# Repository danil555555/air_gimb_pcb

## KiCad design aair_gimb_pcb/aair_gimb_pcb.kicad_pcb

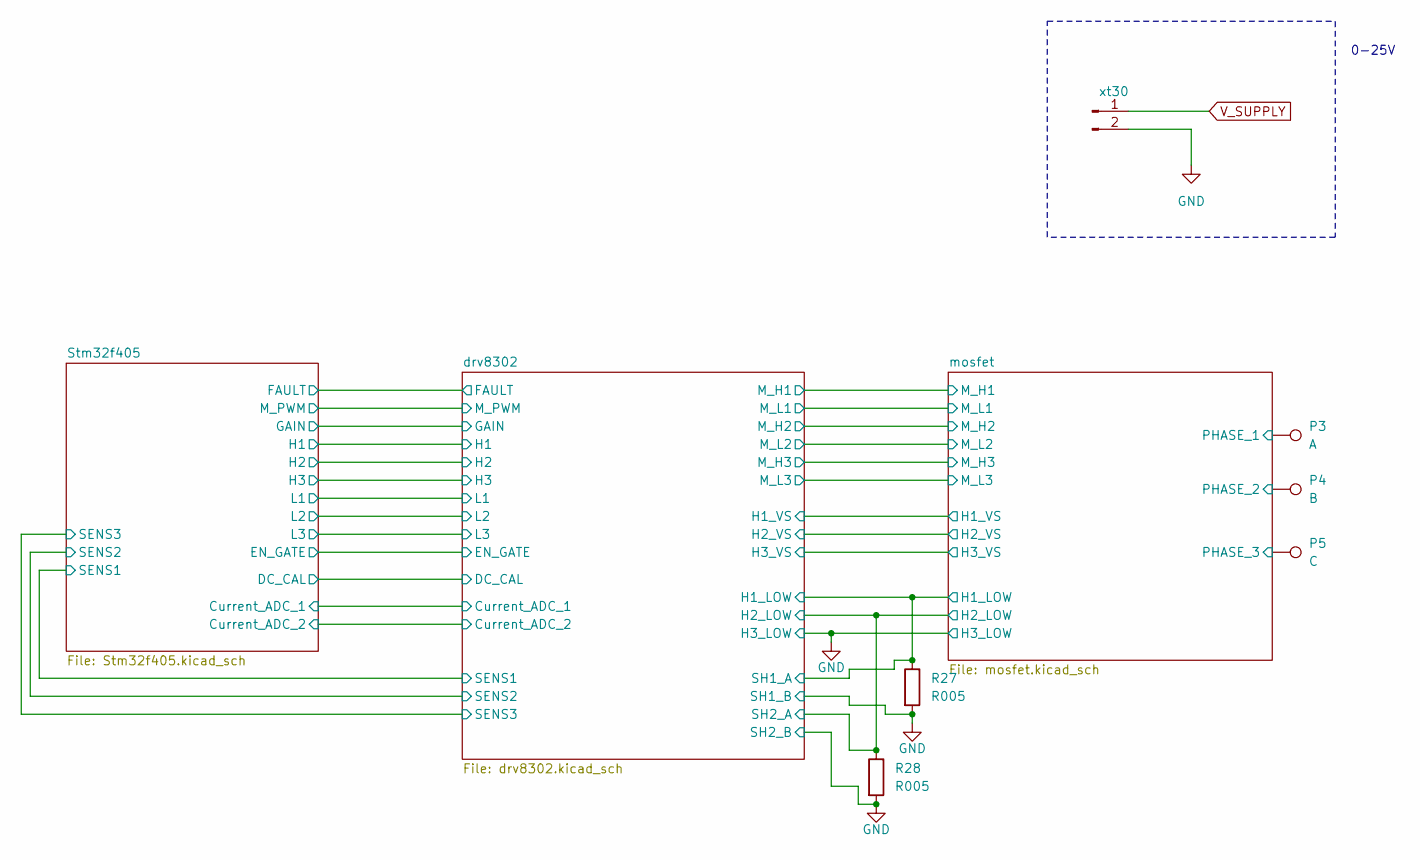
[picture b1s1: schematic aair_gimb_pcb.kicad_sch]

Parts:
P3: A; 1PAD_4x5mm
P4: B; 1PAD_4x5mm
P5: C; 1PAD_4x5mm
R27, R28: R005; R_2512_6332Metric
xt30: XT30; AMASS_XT30PW-M_1x02_P2.50mm_Horizontal

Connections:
/drv8302/H1_LOW: R27.1; also elsewhere on the board
/drv8302/H2_LOW: R28.1; also elsewhere on the board
GND: R27.2, R28.2, xt30.2; also elsewhere on the board
V_SUPPLY: xt30.1; also elsewhere on the board

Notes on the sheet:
0-25V

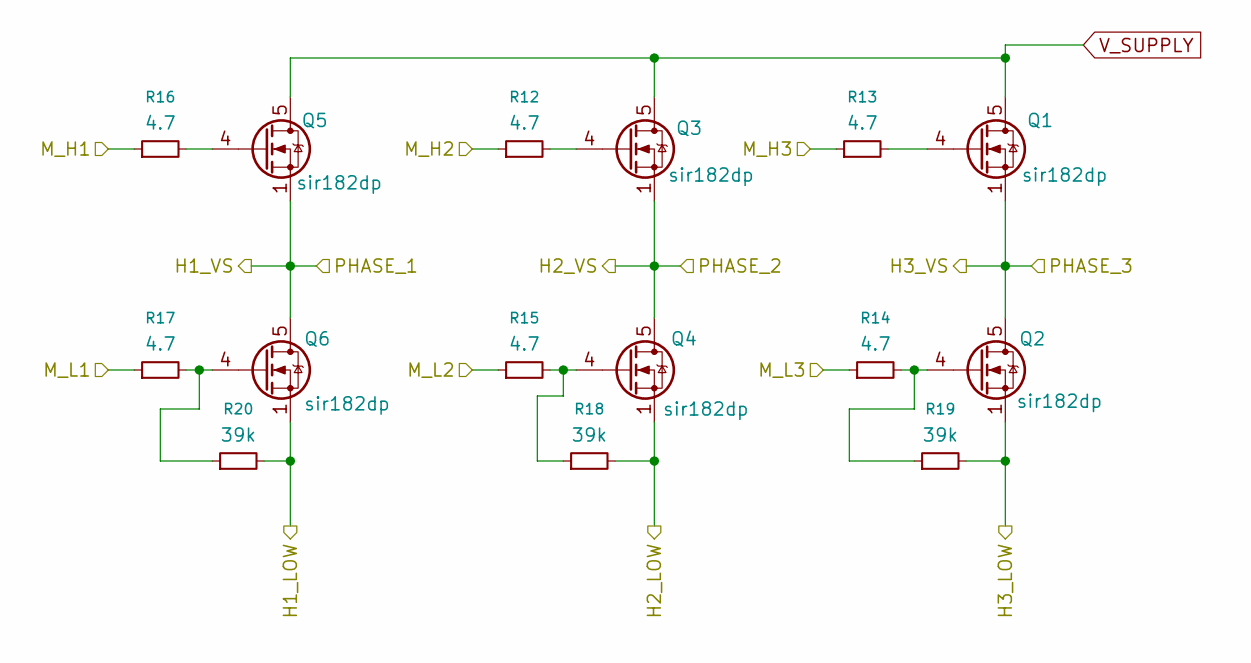
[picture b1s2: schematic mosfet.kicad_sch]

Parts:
Q1, Q2, Q3, Q4, Q5, Q6: sir182dp; PowerPAK_SO-8_Single
R12, R13, R14, R15, R16, R17: 4.7; R_0603_1608Metric
R18, R19, R20: 39k; R_0603_1608Metric

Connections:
/drv8302/H1_LOW: Q6.1 (S), Q6.2 (S), Q6.3 (S), R20.2; also elsewhere on the board
/drv8302/H1_VS: Q5.1 (S), Q5.2 (S), Q5.3 (S), Q6.5 (D); also elsewhere on the board
/drv8302/H2_LOW: Q4.1 (S), Q4.2 (S), Q4.3 (S), R18.2; also elsewhere on the board
/drv8302/H2_VS: Q3.1 (S), Q3.2 (S), Q3.3 (S), Q4.5 (D); also elsewhere on the board
/drv8302/H3_VS: Q1.1 (S), Q1.2 (S), Q1.3 (S), Q2.5 (D); also elsewhere on the board
/drv8302/M_H1: R16.1; also elsewhere on the board
/drv8302/M_H2: R12.1; also elsewhere on the board
/drv8302/M_H3: R13.1; also elsewhere on the board
/drv8302/M_L1: R17.1; also elsewhere on the board
/drv8302/M_L2: R15.1; also elsewhere on the board
/drv8302/M_L3: R14.1; also elsewhere on the board
GND: Q2.1 (S), Q2.2 (S), Q2.3 (S), R19.2; also elsewhere on the board
unnamed: Q1.4 (G), R13.2
unnamed: Q2.4 (G), R14.2, R19.1
unnamed: Q3.4 (G), R12.2
unnamed: Q4.4 (G), R15.2, R18.1
unnamed: Q5.4 (G), R16.2
unnamed: Q6.4 (G), R17.2, R20.1
V_SUPPLY: Q1.5 (D), Q3.5 (D), Q5.5 (D); also elsewhere on the board

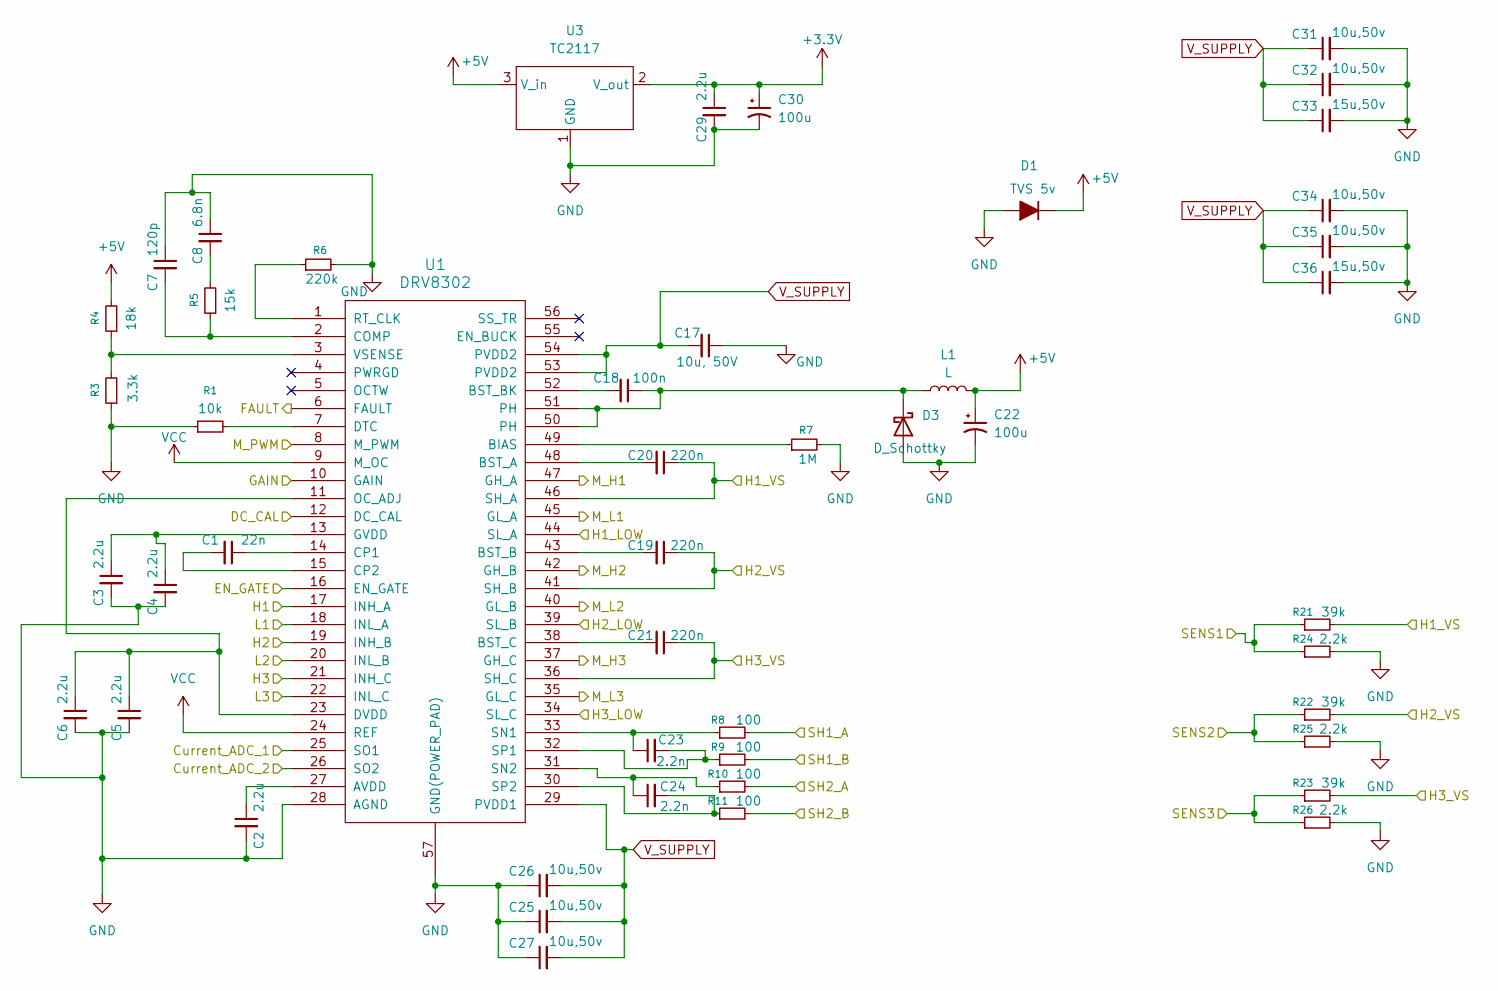
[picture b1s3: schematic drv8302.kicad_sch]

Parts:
C1: 22n; SMD-0603_r
C2, C3, C4, C6, C29: 2.2u; SMD-0603_r
C5: 2.2u; SMD-0603_c
C7: 120p; SMD-0603_r
C8: 6.8n; SMD-0603_r
C17: 10u, 50V; SMD-1206
C18: 100n; SMD-0603_r
C19, C20, C21: 220n; SMD-0603_r
C22, C30: 100u; CP_EIA-3528-21_Kemet-B
C23, C24: 2.2n; SMD-0603_r
C25, C26, C27, C31, C32, C34, C35: 10u,50v; C_1206_3216Metric
C33, C36: 15u,50v; C_1206_3216Metric
D1: TVS 5v; D_SMA
D3: D_Schottky; D_SMA
L1: L; L_7.3x7.3_H4.5
R1: 10k; SMD-0603_r
R3: 3.3k; SMD-0603_r
R4: 18k; SMD-0603_r
R5: 15k; SMD-0603_r
R6: 220k; SMD-0603_r
R7: 1M; SMD-0603_r
R8, R9, R10, R11: 100; SMD-0603_r
R21, R22, R23: 39k; SMD-0603_r
R24, R25, R26: 2.2k; SMD-0603_r
U1: DRV8302; HTSSOP-56-1EP_6.1x14mm_P0.5mm_EP3.61x6.35mm
U3: TC2117; SOT-223

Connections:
+3.3V: C29.1, C30.1, U3.2 (V_out); also elsewhere on the board
+5V: C22.1, D1.1 (K), L1.2, R4.2, U3.3 (V_in); also elsewhere on the board
/Stm32f405/Current_ADC_1: U1.25 (SO1); also elsewhere on the board
/Stm32f405/Current_ADC_2: U1.26 (SO2); also elsewhere on the board
/Stm32f405/DC_CAL: U1.12 (DC_CAL); also elsewhere on the board
/Stm32f405/EN_GATE: U1.16 (EN_GATE); also elsewhere on the board
/Stm32f405/FAULT: U1.6 (FAULT); also elsewhere on the board
/Stm32f405/GAIN: U1.10 (GAIN); also elsewhere on the board
/Stm32f405/H1: U1.17 (INH_A); also elsewhere on the board
/Stm32f405/H2: U1.19 (INH_B); also elsewhere on the board
/Stm32f405/H3: U1.21 (INH_C); also elsewhere on the board
/Stm32f405/L1: U1.18 (INL_A); also elsewhere on the board
/Stm32f405/L2: U1.20 (INL_B); also elsewhere on the board
/Stm32f405/L3: U1.22 (INL_C); also elsewhere on the board
/Stm32f405/M_PWM: U1.8 (M_PWM); also elsewhere on the board
/Stm32f405/SENS1: R21.1, R24.1; also elsewhere on the board
/Stm32f405/SENS2: R22.1, R25.1; also elsewhere on the board
/Stm32f405/SENS3: R23.1, R26.1; also elsewhere on the board
/drv8302/H1_LOW: R8.2, U1.44 (SL_A); also elsewhere on the board
/drv8302/H1_VS: C20.1, R21.2, U1.46 (SH_A); also elsewhere on the board
/drv8302/H2_LOW: R10.2, U1.39 (SL_B); also elsewhere on the board
/drv8302/H2_VS: C19.1, R22.2, U1.41 (SH_B); also elsewhere on the board
/drv8302/H3_VS: C21.1, R23.2, U1.36 (SH_C); also elsewhere on the board
/drv8302/M_H1: U1.47 (GH_A); also elsewhere on the board
/drv8302/M_H2: U1.42 (GH_B); also elsewhere on the board
/drv8302/M_H3: U1.37 (GH_C); also elsewhere on the board
/drv8302/M_L1: U1.45 (GL_A); also elsewhere on the board
/drv8302/M_L2: U1.40 (GL_B); also elsewhere on the board
/drv8302/M_L3: U1.35 (GL_C); also elsewhere on the board
GND: C2.2, C3.2, C4.2, C5.2, C6.2, C7.1, C8.1, C17.1, C22.2, C25.1, C26.1, C27.1, C29.2, C30.2, C31.2, C32.2, C33.2, C34.2, C35.2, C36.2, D1.2 (A), D3.2 (A), R1.1, R3.1, R6.2, R7.2, R9.2, R11.2, R24.2, R25.2, R26.2, U1.28 (AGND), U1.34 (SL_C), U1.57 (GND(POWER_PAD)), U3.1 (GND); also elsewhere on the board
unnamed: C8.2, R5.2
unnamed: C18.1, D3.1 (K), L1.1, U1.50 (PH), U1.51 (PH)
unnamed: C2.1, U1.27 (AVDD)
unnamed: R7.1, U1.49 (BIAS)
unnamed: C20.2, U1.48 (BST_A)
unnamed: C19.2, U1.43 (BST_B)
unnamed: C18.2, U1.52 (BST_BK)
unnamed: C21.2, U1.38 (BST_C)
unnamed: C7.2, R5.1, U1.2 (COMP)
unnamed: C1.1, U1.14 (CP1)
unnamed: C1.2, U1.15 (CP2)
unnamed: R1.2, U1.7 (DTC)
unnamed: C5.1, C6.1, U1.11 (OC_ADJ), U1.23 (DVDD)
unnamed: C3.1, C4.1, U1.13 (GVDD)
unnamed: R6.1, U1.1 (RT_CLK)
unnamed: C23.1, R8.1, U1.33 (SN1)
unnamed: C24.1, R10.1, U1.31 (SN2)
unnamed: C23.2, R9.1, U1.32 (SP1)
unnamed: C24.2, R11.1, U1.30 (SP2)
unnamed: R3.2, R4.1, U1.3 (VSENSE)
VCC: U1.9 (M_OC), U1.24 (REF)
V_SUPPLY: C17.2, C25.2, C26.2, C27.2, C31.1, C32.1, C33.1, C34.1, C35.1, C36.1, U1.29 (PVDD1), U1.53 (PVDD2), U1.54 (PVDD2); also elsewhere on the board

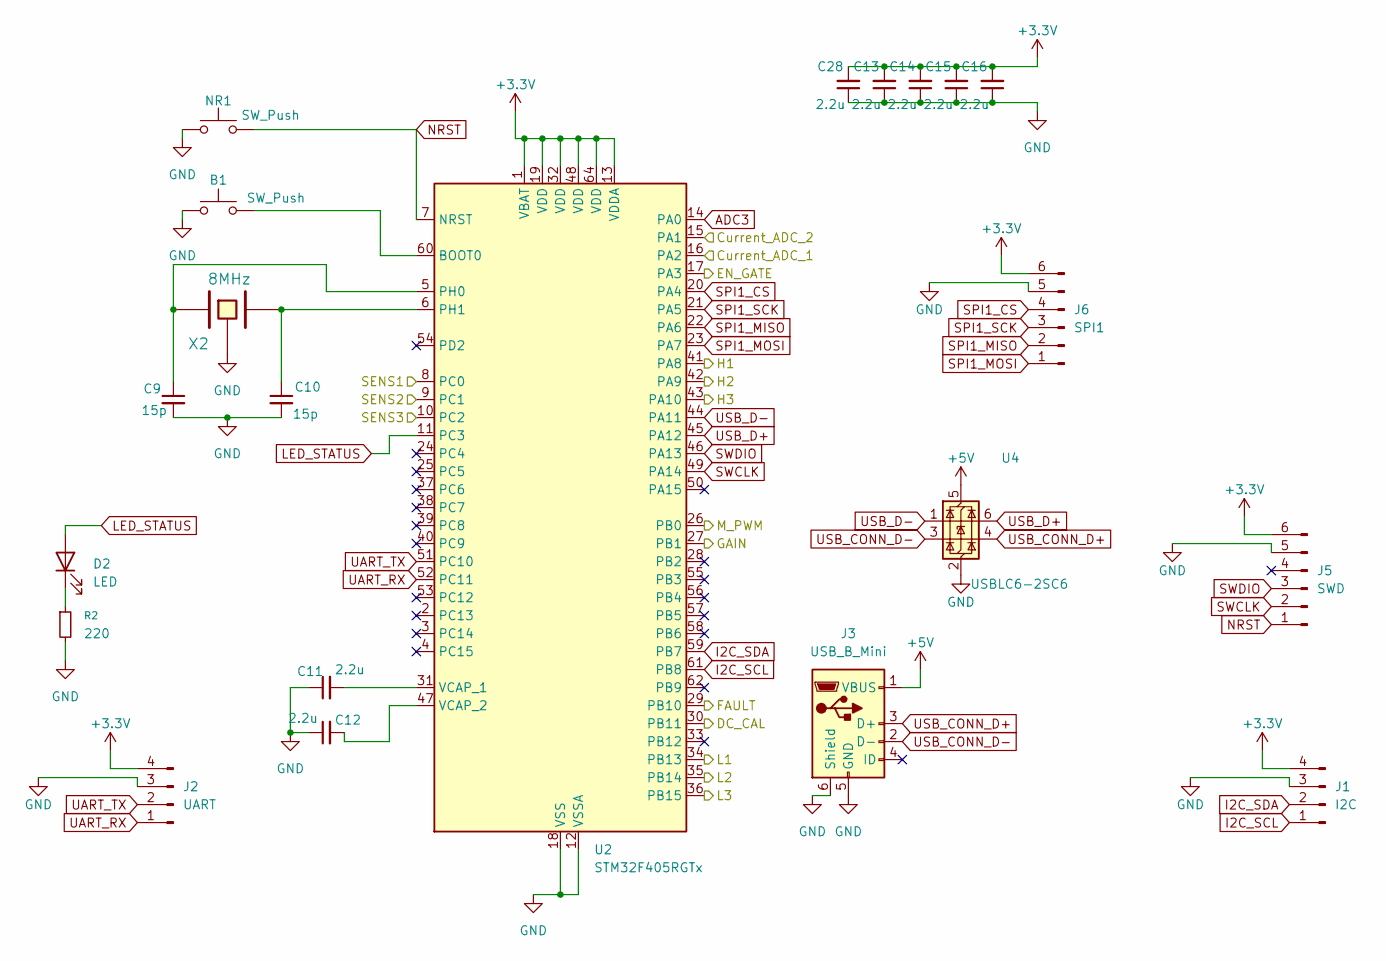
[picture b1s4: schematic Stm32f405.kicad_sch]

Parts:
B1: SW_Push; SW_Push_1P1T_NO_CK_KMR2
C9, C10: 15p; SMD-0603_c
C11, C12, C13, C14, C15, C16, C28: 2.2u; SMD-0603_c
D2: LED; LED_0603_1608Metric
J1: I2C; JST_GH_BM04B-GHS-TBT_1x04-1MP_P1.25mm_Vertical
J2: UART; JST_GH_BM04B-GHS-TBT_1x04-1MP_P1.25mm_Vertical
J3: USB_B_Mini; USB_Mini-B_Lumberg_2486_01_Horizontal
J5: SWD; JST_GH_BM06B-GHS-TBT_1x06-1MP_P1.25mm_Vertical
J6: SPI1; JST_GH_BM06B-GHS-TBT_1x06-1MP_P1.25mm_Vertical
NR1: SW_Push; SW_Push_1P1T_NO_CK_KMR2
R2: 220; R_0603_1608Metric
U2: STM32F405RGTx; LQFP-64_10x10mm_P0.5mm
U4: USBLC6-2SC6; SOT-23-6; LCSC Part # C7519
X2: 8MHz; Crystal_5x3mm

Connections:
+3.3V: C13.2, C14.2, C15.2, C16.2, C28.2, J1.4, J2.4, J5.6, J6.6, U2.1 (VBAT), U2.13 (VDDA), U2.19 (VDD), U2.32 (VDD), U2.48 (VDD), U2.64 (VDD); also elsewhere on the board
+5V: J3.1 (VBUS), U4.5 (VBUS); also elsewhere on the board
/Stm32f405/Current_ADC_1: U2.16 (PA2); also elsewhere on the board
/Stm32f405/Current_ADC_2: U2.15 (PA1); also elsewhere on the board
/Stm32f405/DC_CAL: U2.30 (PB11); also elsewhere on the board
/Stm32f405/EN_GATE: U2.17 (PA3); also elsewhere on the board
/Stm32f405/FAULT: U2.29 (PB10); also elsewhere on the board
/Stm32f405/GAIN: U2.27 (PB1); also elsewhere on the board
/Stm32f405/H1: U2.41 (PA8); also elsewhere on the board
/Stm32f405/H2: U2.42 (PA9); also elsewhere on the board
/Stm32f405/H3: U2.43 (PA10); also elsewhere on the board
/Stm32f405/L1: U2.34 (PB13); also elsewhere on the board
/Stm32f405/L2: U2.35 (PB14); also elsewhere on the board
/Stm32f405/L3: U2.36 (PB15); also elsewhere on the board
/Stm32f405/M_PWM: U2.26 (PB0); also elsewhere on the board
/Stm32f405/SENS1: U2.8 (PC0); also elsewhere on the board
/Stm32f405/SENS2: U2.9 (PC1); also elsewhere on the board
/Stm32f405/SENS3: U2.10 (PC2); also elsewhere on the board
ADC3: U2.14 (PA0)
GND: B1.1, C9.2, C10.2, C11.1, C12.1, C13.1, C14.1, C15.1, C16.1, C28.1, J1.3, J1.MP, J2.3, J2.MP, J3.5 (GND), J3.6 (Shield), J5.5, J5.MP, J6.5, J6.MP, NR1.1, R2.2, U2.12 (VSSA), U2.18 (VSS), U2.63 (VSS), U4.2 (GND), X2.3 (GND); also elsewhere on the board
I2C_SCL: J1.1, U2.61 (PB8)
I2C_SDA: J1.2, U2.59 (PB7)
LED_STATUS: D2.2 (A), U2.11 (PC3)
NRST: J5.1, NR1.2, U2.7 (NRST)
unnamed: D2.1 (K), R2.1
unnamed: B1.2, U2.60 (BOOT0)
unnamed: C9.1, U2.5 (PH0), X2.1
unnamed: C10.1, U2.6 (PH1), X2.2
unnamed: C11.2, U2.31 (VCAP_1)
unnamed: C12.2, U2.47 (VCAP_2)
SPI1_CS: J6.4, U2.20 (PA4)
SPI1_MISO: J6.2, U2.22 (PA6)
SPI1_MOSI: J6.1, U2.23 (PA7)
SPI1_SCK: J6.3, U2.21 (PA5)
SWCLK: J5.2, U2.49 (PA14)
SWDIO: J5.3, U2.46 (PA13)
UART_RX: J2.1, U2.52 (PC11)
UART_TX: J2.2, U2.51 (PC10)
USB_CONN_D+: J3.3 (D+), U4.4 (I/O2)
USB_CONN_D-: J3.2 (D-), U4.3 (I/O2)
USB_D+: U2.45 (PA12), U4.6 (I/O1)
USB_D-: U2.44 (PA11), U4.1 (I/O1)

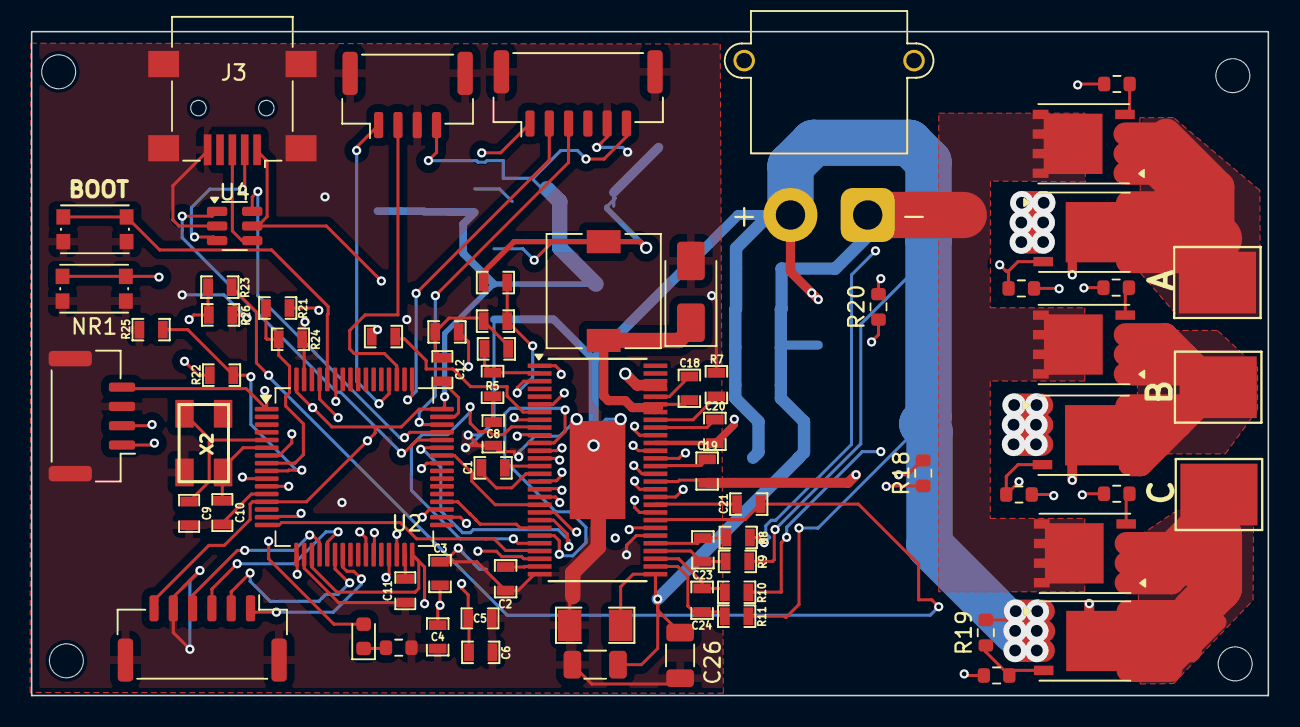
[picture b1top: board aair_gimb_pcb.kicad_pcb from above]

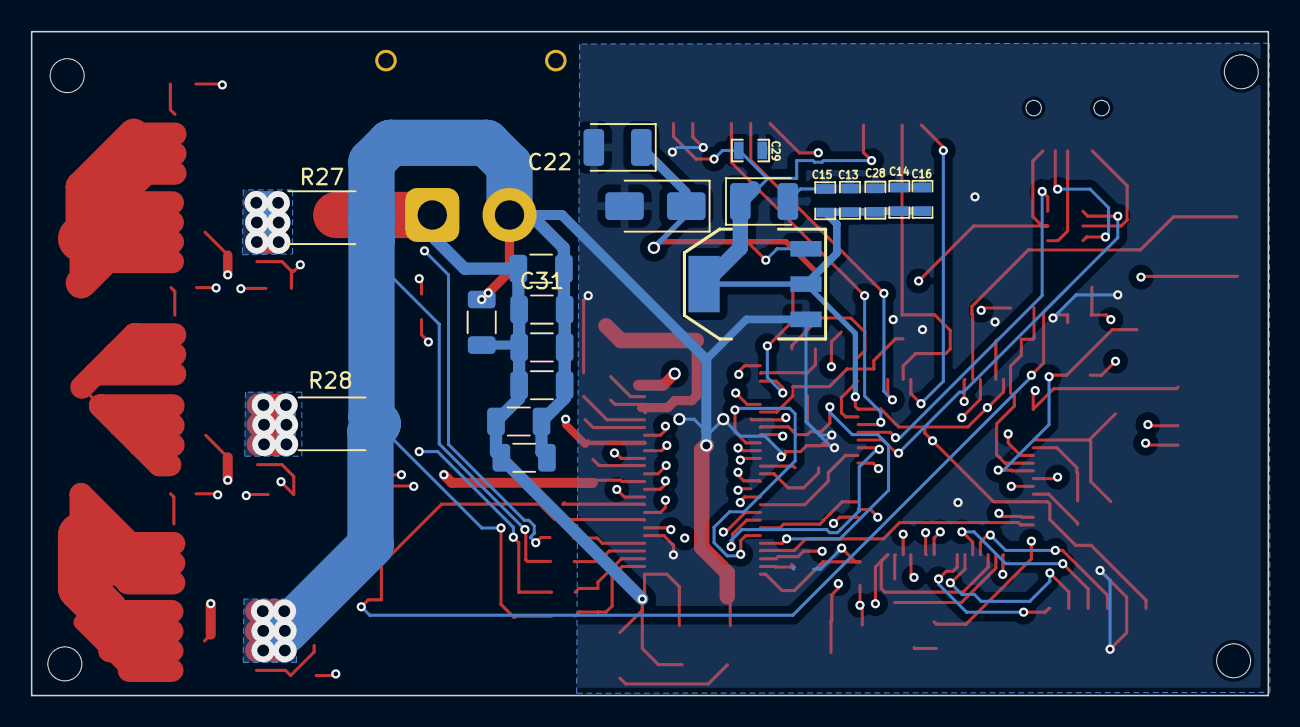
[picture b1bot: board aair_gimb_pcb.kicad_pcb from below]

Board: 4 copper layers, 80.1 x 43.0 mm, 90 parts (19 on the bottom side), 80 nets.

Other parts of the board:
A: A; 1PAD_4x5mm
B: B; 1PAD_4x5mm
C: C; 1PAD_4x5mm

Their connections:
/drv8302/H1_VS: A.1; also elsewhere on the board
/drv8302/H2_VS: B.1; also elsewhere on the board
/drv8302/H3_VS: C.1; also elsewhere on the board

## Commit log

2025-10-16 create stm32
2025-10-16 mac update
2025-10-17 macros
2025-10-17 add mosfet
2025-10-18 добавить пины стм, диод, питание 3.3, разъемы
2025-10-18 сделать коннектор для переыерии
2025-10-20 add digital logic to pcb
2025-10-21 fix exeption to pcb
2025-10-21 done
2025-10-21 готово
2025-10-22 pcb, step
